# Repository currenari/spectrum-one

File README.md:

# Spectrum One

Spectrum One is a compact ESP32-based WiFi activity monitor that visualises nearby WiFi activity using a 16×2 LCD and a 10-segment LED bar.

It works by running repeated WiFi scans and turning the results into something you can actually see — live signal bars, changing numbers, blinking LEDs. The values shown are derived from WiFi RSSI and are intended for visualisation and comparison, not calibrated RF measurement.

This repository contains the reference implementation of the device.

---

## Open Hardware Certification

**OSHWA UID:** UK000086  
Full record: `CERTIFICATION.md`  
Certified hardware version: 0.1.0

---

## Repository Contents

The repository is organised by release version and contains:

**binaries/**  
Versioned reference firmware binaries for flashing Spectrum One hardware.

**firmware/**  
ESP-IDF firmware source code.

**hardware/**  
KiCad schematics, PCB layouts, symbols, footprints, and fabrication outputs.

**docs/**  
Repository documentation, technical notes, and [ESP32 WiFi Activity Monitor PDF Book (Direct Download)](https://github.com/currenari/spectrum-one/raw/main/docs/ESP32%20WiFi%20Activity%20Monitor.pdf).

**media/**  
Images and diagrams used by the repository documentation.

---

## Hardware Assembly

This repository provides assembly documentation sufficient to reproduce the open hardware design.

General assembly information is provided in:

`ASSEMBLY.md`

Version-specific assembly notes are located under:

- `hardware/v0.1.0/ASSEMBLY.md`

---

## Project Scope

This repository contains the open hardware design files, firmware source code, reference binaries, and technical documentation required to reproduce Spectrum One.

Extended development notes and technical writing are published at:

https://currenari.com

---

## Licensing

Licensing is separated by material type:

- **Firmware source code and binaries**  
  MIT License

- **Hardware design files**  
  CERN Open Hardware Licence v2.0 – Strongly Reciprocal (CERN-OHL-S-2.0)

- **Repository documentation and media**  
  Creative Commons Attribution 4.0 International (CC BY 4.0)

Full licensing terms are defined in `LICENSE.md`.

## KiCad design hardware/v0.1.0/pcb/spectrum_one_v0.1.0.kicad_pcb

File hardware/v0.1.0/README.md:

# Spectrum One Hardware v0.1.0

This folder contains the KiCad design files for Spectrum One hardware release v0.1.0.

Contents include:
- Schematic
- PCB layout
- Custom symbols and footprints
- Fabrication outputs (Gerbers and drill files)

The Gerbers in hardware/v0.1.0/gerbers are the release fabrication set for this version.

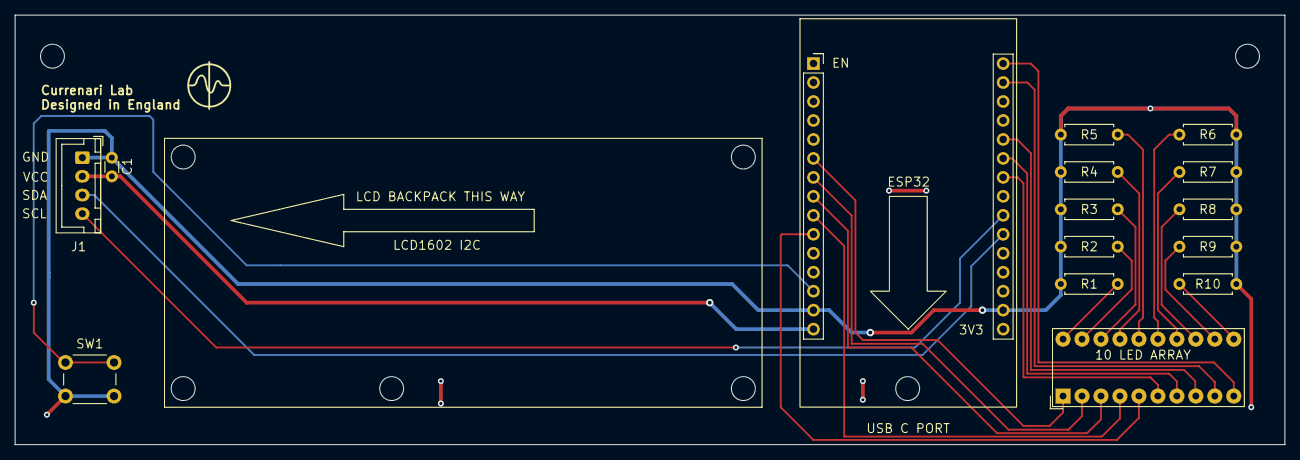
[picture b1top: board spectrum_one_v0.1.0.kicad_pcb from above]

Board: 2 copper layers, 170.0 x 57.5 mm, 15 parts (0 on the bottom side), 25 nets.

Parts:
10 LED ARRAY: HLCP-J100_2; HLCP-J100
C1: C; C_Disc_D3.0mm_W1.6mm_P2.50mm
ESP32: Copper Keepout Zone; ESP32_DEVKIT_V1_DUAL_HEADER_SOCKET_VERTICAL
J1: LCD_I2C_XH4_PCBSocket; JST_XH_B4B-XH-A_1x04_P2.50mm_Vertical
R1, R2, R3, R4, R5, R6, R7, R8, R9, R10: R; R_Axial_DIN0207_L6.3mm_D2.5mm_P7.62mm_Horizontal
SW1: SW_Tact_6x6mm_H5mm_PxPy; SW_Tact_6x6mm_H5mm_PxPy_footprint

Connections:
/VCC: C1.2, ESP32.15 (VIN), J1.2 (VCC)
GND: C1.1, ESP32.14 (GND), ESP32.29 (GND), J1.1 (GND), R1.1, R2.1, R3.1, R4.1, R5.1, R6.1, R7.1, R8.1, R9.1, R10.1, SW1.2
unnamed: 10 LED ARRAY.11 (K), R10.2
unnamed: 10 LED ARRAY.12 (K), R9.2
unnamed: 10 LED ARRAY.13 (K), R8.2
unnamed: 10 LED ARRAY.14 (K), R7.2
unnamed: 10 LED ARRAY.15 (K), R6.2
unnamed: 10 LED ARRAY.16 (K), R5.2
unnamed: 10 LED ARRAY.17 (K), R4.2
unnamed: 10 LED ARRAY.18 (K), R3.2
unnamed: 10 LED ARRAY.19 (K), R2.2
unnamed: 10 LED ARRAY.20 (K), R1.2
unnamed: ESP32.24 (GPIO17), J1.4 (SCL)
unnamed: ESP32.25 (GPIO16), J1.3 (SDA)
unnamed: ESP32.13 (GPIO13), SW1.1
unnamed: 10 LED ARRAY.6 (A), ESP32.22 (GPIO18)
unnamed: 10 LED ARRAY.7 (A), ESP32.21 (GPIO19)
unnamed: 10 LED ARRAY.8 (A), ESP32.20 (GPIO21)
unnamed: 10 LED ARRAY.9 (A), ESP32.17 (GPIO22)
unnamed: 10 LED ARRAY.10 (A), ESP32.16 (GPIO23)
unnamed: 10 LED ARRAY.3 (A), ESP32.8 (GPIO25)
unnamed: 10 LED ARRAY.4 (A), ESP32.9 (GPIO26)
unnamed: 10 LED ARRAY.5 (A), ESP32.10 (GPIO27)
unnamed: 10 LED ARRAY.1 (A), ESP32.6 (GPIO32)
unnamed: 10 LED ARRAY.2 (A), ESP32.7 (GPIO33)

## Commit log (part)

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2026-01-13 Initial Spectrum One v0.1.0
2026-01-13 Add gitignore
2026-01-13 Update README to reflect current repository structure
2026-01-13 Add overview and versioned READMEs; fix pcb folder name
2026-01-14 test: enable signed commits
2026-01-14 test: signed commit
2026-01-14 update BOM: complete hardware listing
2026-01-14 Finalize documentation and licensing for OSHWA open hardware compliance
2026-01-15 add assembly docs and photos
2026-01-15 update PCB assembly documentation
2026-01-16 add OSHWA open hardware certification (UK000086)
2026-02-09 Revise README for second edition free release
    Book is now available as a free PDF/EPUB download under CC BY-NC-SA 4.0. Updated licensing section and added direct download link to currenari.com/spectrum-one.
2026-02-09 Revise licensing terms and clarify book distribution
    Updated README and LICENSE to reflect the book now available as a free PDF/EPUB download at currenari.com/spectrum-one under Creative Commons Attribution–NonCommercial–ShareAlike 4.0.
2026-02-09 README update — book second edition free release under CC BY-NC-SA 4.0
    Updated README and LICENSE to reflect the book now available as a free PDF/EPUB download at currenari.com/spectrum-one under Creative Commons Attribution–NonCommercial–ShareAlike 4.0.
2026-02-12 Add image to README for visual enhancement
    Added an image to enhance the visual representation of the project.
2026-02-27 Add header image and update README
